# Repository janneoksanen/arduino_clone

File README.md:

# arduino_clone
Battery powered Arduino clone with RTC clock and extraa EEPROM

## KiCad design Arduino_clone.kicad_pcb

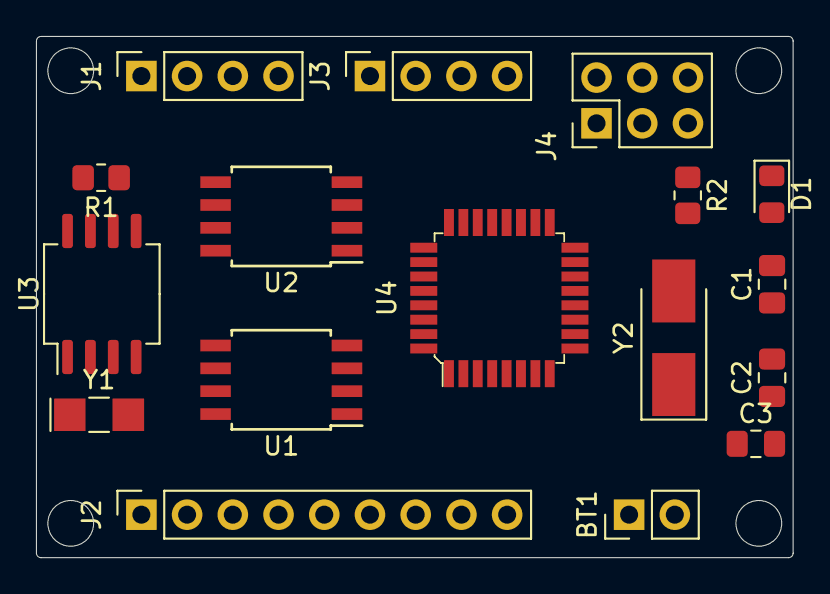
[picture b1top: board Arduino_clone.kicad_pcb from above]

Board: 2 copper layers, 42.0 x 29.0 mm, 17 parts (0 on the bottom side), 24 nets, no tracks yet.

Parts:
BT1: 3V; PinHeader_1x02_P2.54mm_Vertical
C1, C2: 22pF; C_0805_2012Metric_Pad1.18x1.45mm_HandSolder
C3: 10uF; C_0805_2012Metric_Pad1.18x1.45mm_HandSolder
D1: LED; LED_0805_2012Metric_Pad1.15x1.40mm_HandSolder
J1: Serial; PinSocket_1x04_P2.54mm_Vertical
J2: Digital pins; PinSocket_1x09_P2.54mm_Vertical
J3: I2C; PinSocket_1x04_P2.54mm_Vertical
J4: ICSP; PinHeader_2x03_P2.54mm_Vertical
R1: 10k; R_0805_2012Metric_Pad1.20x1.40mm_HandSolder
R2: 330; R_0805_2012Metric_Pad1.20x1.40mm_HandSolder
U1, U2: 24LC1025; SOIJ-8_5.3x5.3mm_P1.27mm
U3: DS1337S+; SO-8_5.3x6.2mm_P1.27mm
U4: ATMEGA328P-AU; TQFP-32_7x7mm
Y1: 32 MHz; Crystal_SMD_MicroCrystal_CC7V-T1A-2Pin_3.2x1.5mm_HandSolder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
Y2: 16 MHz; Crystal_SMD_5032-2Pin_5.0x3.2mm_HandSoldering

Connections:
/A0: U1.1, U2.1, U4.23
/A1: U1.2, U2.2, U4.24
/D2: J2.1, U4.32
/D3: J2.2, U4.1
/D4: J2.3, U4.2
/D5: J2.4, U4.9
/D6: J2.5, U4.10
/D7: J2.6, U4.11
/D8: J2.7, U4.12
/MISO: J4.1, U4.16
/MOSI: J4.4, U4.15
/RST: J4.5, R1.1, U4.29
/Rx: J1.3, U4.30
/SCK: D1.2, J3.4, J4.3, U4.17
/SCL: U1.6, U2.6, U3.6, U4.28
/SDA: J3.3, U1.5, U2.5, U3.5, U4.27
/Tx: J1.4, U4.31
/Vcc: BT1.1, C3.1, J1.2, J2.9, J3.2, J4.2, R1.2, U1.3, U1.8, U2.3, U2.8, U3.3, U3.8, U4.4, U4.6, U4.18, U4.20
GNDPWR: BT1.2, C1.2, C2.2, C3.2, J1.1, J2.8, J3.1, J4.6, R2.2, U1.4, U1.7, U2.4, U2.7, U3.4, U4.3, U4.5, U4.21
unnamed: C1.1, U4.7, Y2.2
unnamed: C2.1, U4.8, Y2.1
unnamed: D1.1, R2.1
unnamed: U3.1, Y1.1
unnamed: U3.2, Y1.2

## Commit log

2021-02-26 Schematic page settings entered
2021-02-26 Added sheet for connectors
2021-02-26 Most components added to sheets
2021-02-27 Created a custom symbol for DS1337 and used it in the schematic
2021-02-27 All components added to schematic
2021-02-27 Components organized in schematic
2021-02-27 Components annotated in schematic
2021-02-27 Footprints assigned
2021-03-01 Added component values to schematic
2021-03-01 ICSP connector wired up in schematic
2021-03-02 Connectors schematic sheet wired
2021-03-04 Schematic all wired up
2021-03-05 Added comments to schematic
2021-03-05 Created netlist file
2021-03-06 Layout page settings done
2021-03-06 Layout design rules edited
2021-03-07 Initial component placement done
2021-03-11 Board outline drawn
2021-03-21 Mounting holes added
2021-03-21 Changed ICSP connector footprint from female to male
2021-03-22 2-layer routing complete
2021-05-20 4 layer routing completed
2021-05-20 Added ground fill to 4-layer design
2021-05-20 Added ground fill to 2-layer design
